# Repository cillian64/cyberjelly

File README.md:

# cyberjelly
Driver code for the EMF 2022 Null Sector CyberJellies

Credit to Chris / elsmorian for the overall hardware design and PCBs, and to
the many people who helped actually build the things.

Requires the `adafruit-circuitpython-raspberry_pi_pico-en_GB-7.3.0.uf2`
firmware be loaded onto the Raspberry Pi Pico before the Python code.  After
this, the CircuitPython LED Animation library must be copied into the `lib`
directory on the Pico along with `code.py`, `hsv.py`, and `neopio.py`.

The `mini_jellies` directory contains designs for a miniature version of the
jellyfish.  The head is made from laser-cut 2mm acrylic and half of a 16cm
clear Christmas bauble.  Each tentacle is a 50cm length of 60LED/m WS2812b LED
strip.  The `code.py` file in the `mini_jellies` directory contains modified
firmware for the miniature jellies.

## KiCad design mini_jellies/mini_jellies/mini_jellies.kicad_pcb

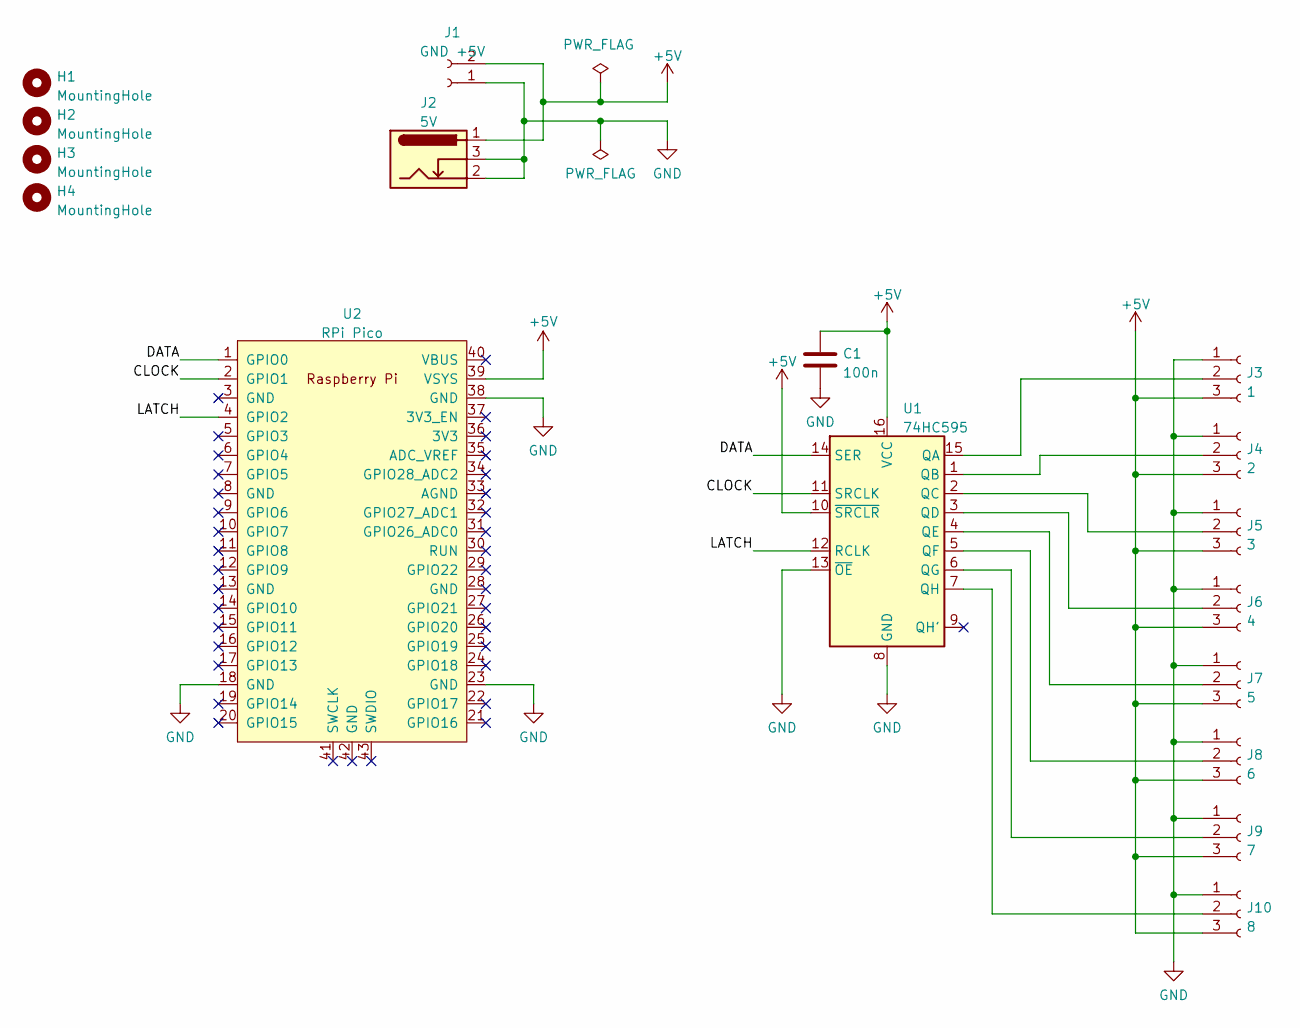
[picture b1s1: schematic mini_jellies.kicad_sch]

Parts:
C1: 100n; C_Disc_D6.0mm_W2.5mm_P5.00mm
H1, H2, H3, H4: MountingHole; MountingHole_3.2mm_M3
J1: GND +5V; SolderWire-1.5sqmm_1x02_P6mm_D1.7mm_OD3mm
J2: 5V; BarrelJack_Horizontal
J3: 1; Molex_KK-254_AE-6410-03A_1x03_P2.54mm_Vertical
J4: 2; Molex_KK-254_AE-6410-03A_1x03_P2.54mm_Vertical
J5: 3; Molex_KK-254_AE-6410-03A_1x03_P2.54mm_Vertical
J6: 4; Molex_KK-254_AE-6410-03A_1x03_P2.54mm_Vertical
J7: 5; Molex_KK-254_AE-6410-03A_1x03_P2.54mm_Vertical
J8: 6; Molex_KK-254_AE-6410-03A_1x03_P2.54mm_Vertical
J9: 7; Molex_KK-254_AE-6410-03A_1x03_P2.54mm_Vertical
J10: 8; Molex_KK-254_AE-6410-03A_1x03_P2.54mm_Vertical
U1: 74HC595; DIP-16_W7.62mm_LongPads
U2: RPi Pico; RPi_Pico_SMD_TH

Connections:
+5V: C1.1, J1.2, J2.1, J3.3, J4.3, J5.3, J6.3, J7.3, J8.3, J9.3, J10.3, U1.10 (~SRCLR), U1.16 (VCC), U2.39 (VSYS)
/CLOCK: U1.11 (SRCLK), U2.2 (GPIO1)
/DATA: U1.14 (SER), U2.1 (GPIO0)
/LATCH: U1.12 (RCLK), U2.4 (GPIO2)
GND: C1.2, J1.1, J2.2, J2.3, J3.1, J4.1, J5.1, J6.1, J7.1, J8.1, J9.1, J10.1, U1.8 (GND), U1.13 (~OE), U2.18 (GND), U2.23 (GND), U2.38 (GND)
unnamed: J3.2, U1.15 (QA)
unnamed: J4.2, U1.1 (QB)
unnamed: J5.2, U1.2 (QC)
unnamed: J6.2, U1.3 (QD)
unnamed: J7.2, U1.4 (QE)
unnamed: J8.2, U1.5 (QF)
unnamed: J9.2, U1.6 (QG)
unnamed: J10.2, U1.7 (QH)

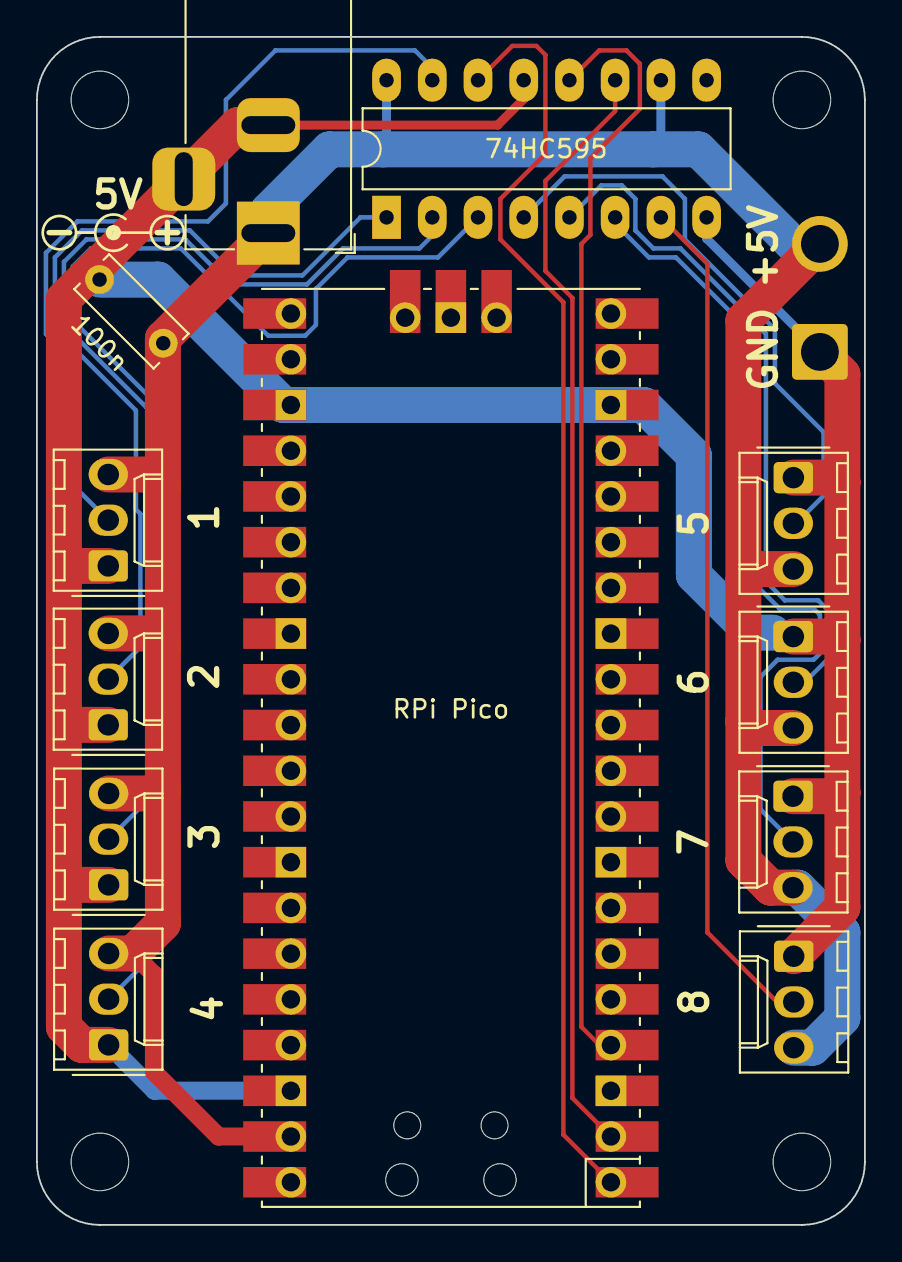
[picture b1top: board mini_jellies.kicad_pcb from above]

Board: 2 copper layers, 46.0 x 66.0 mm, 17 parts (0 on the bottom side), 13 nets.

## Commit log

2022-06-01 Proof of concept code from Steve
2022-06-01 Blue-green fading hue backdrop
2022-06-01 Add ripples
2022-06-01 Randomise ripple order and interval
2022-06-01 Angry mode (work in progress, disabled)
2022-06-10 Add license, fix flake8 violations
2022-06-10 Add photo and credits
2022-09-24 Add PCB for mini-jellies
2022-10-07 Add firmware for mini-jellies
2022-10-07 Fix fw bug and update FPS estimate
2022-10-07 Set 3d model for Pi Pico on PCB
2022-10-16 Finalise mini-jelly firmware
    - Adjust brightness to limit the current to a sensible value
    - Adjust ripple frequency based on FPS adjustment
    - Adjust FPS measurement - the mini-jellies have a lot less LEDs to
    drive and so run ~4 times faster than the big jellies.
2022-10-18 Tweak tentacle/head brightnesses
    Reduce brightnesses of tentacles and increase brightnesses of heads
